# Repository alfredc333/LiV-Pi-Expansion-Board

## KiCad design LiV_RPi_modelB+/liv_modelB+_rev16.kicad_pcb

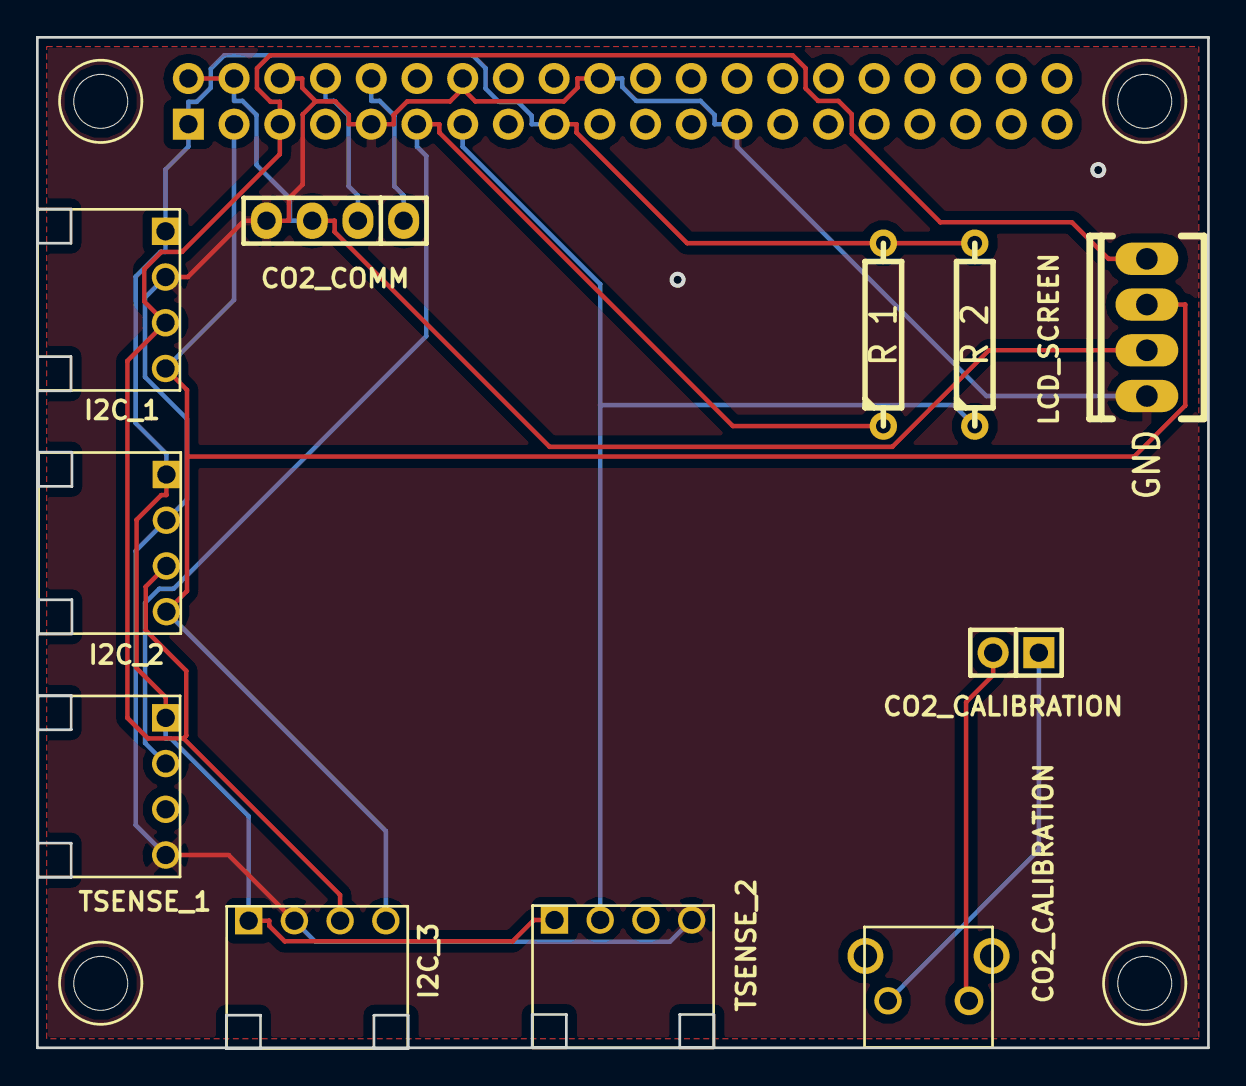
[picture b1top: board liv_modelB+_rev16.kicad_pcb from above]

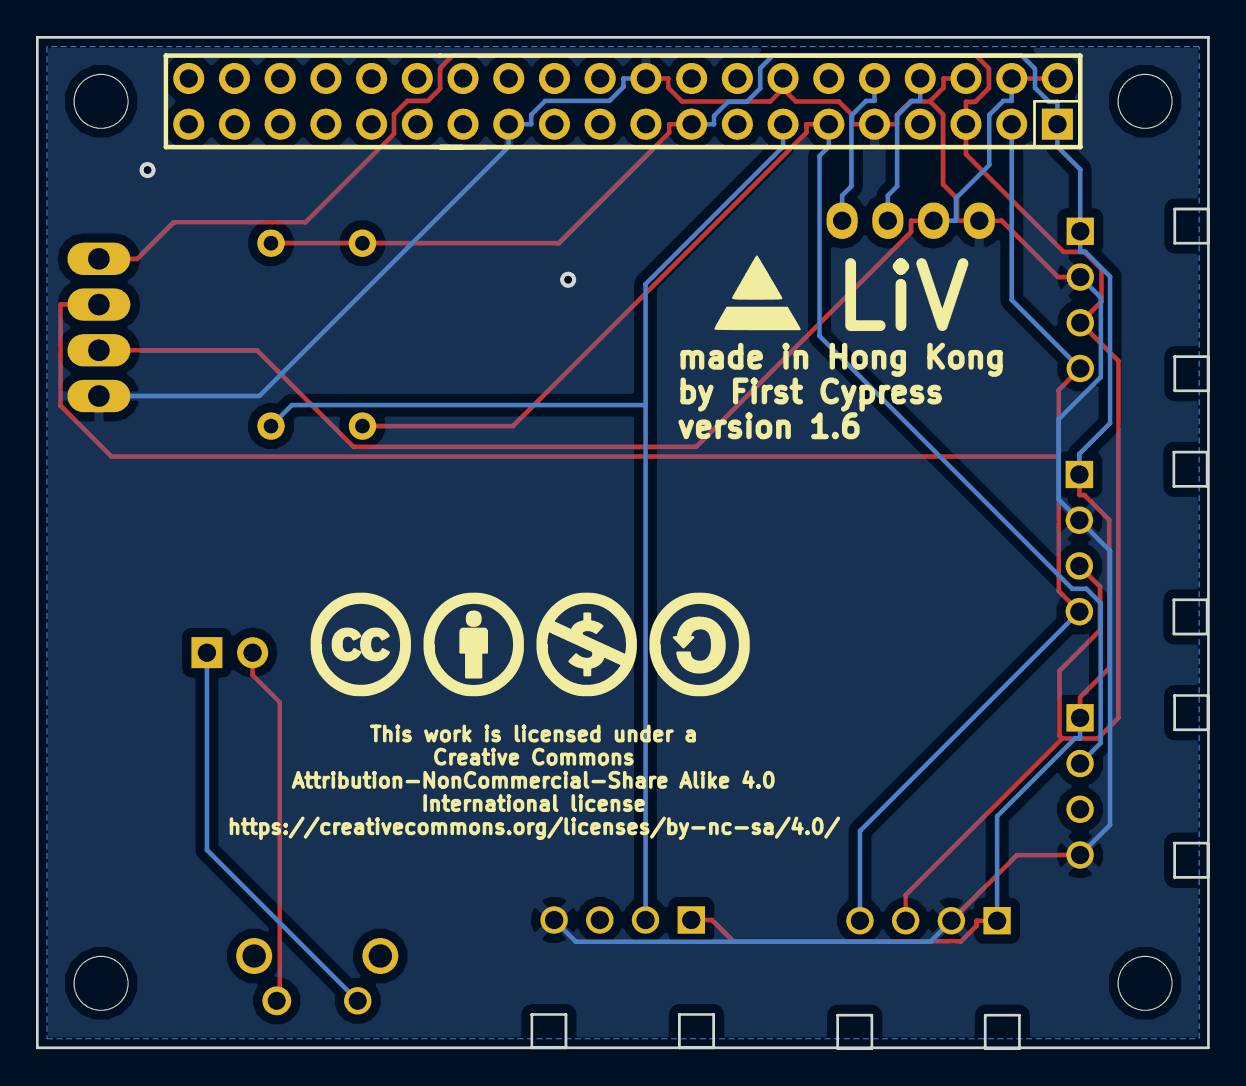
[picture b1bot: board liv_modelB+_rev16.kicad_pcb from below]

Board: 2 copper layers, 65.1 x 56.2 mm, 18 parts (3 on the bottom side), 11 nets.

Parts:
1_MNT_HOLE_RPI_PLUS, 2_MNT_HOLE_RPI_PLUS, 3_MNT_HOLE_RPI_PLUS, 4_MNT_HOLE_RPI_PLUS: mountingHole
R 1, R 2: 10k; R4
cc_by_nc_sa_logo_only: LOGO; cc_by_nc_sa_logo_only
co2_calibration1: CO2_CALIBRATION; SWITCH_TACT_RIGHT_ANGLE
co2_comm: CO2_COMM; Socket_Strip_Straight_1x04
co2_reset1: CO2_CALIBRATION; Socket_Strip_Straight_2x01
i2c_1: I2C_1; CONNECTOR_MOLEX_4PIN_RIGHT_ANGLE
i2c_2: I2C_2; CONNECTOR_MOLEX_4PIN_RIGHT_ANGLE
i2c_3: I2C_3; CONNECTOR_MOLEX_4PIN_RIGHT_ANGLE
liv_cone: LOGO; LivCypressOnlyLogo
rpi40: CONN_20X2; Socket_Strip_Straight_2x13
screen: LCD_SCREEN; Socket_MOLEX-KK-RM2-54mm_Lock_4pin_straight
temp_1: TSENSE_1; CONNECTOR_MOLEX_4PIN_RIGHT_ANGLE
temp_2: TSENSE_2; CONNECTOR_MOLEX_4PIN_RIGHT_ANGLE

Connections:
+3.3V: R 1.2, R 2.2, i2c_1.1, i2c_2.1, i2c_3.1, rpi40.1, rpi40.17, temp_1.1, temp_2.1
+5V: co2_comm.3, rpi40.2, rpi40.4, screen.2
/GPIO_2: i2c_1.4, i2c_2.4, i2c_3.4, rpi40.3, screen.3
/GPIO_3: i2c_1.3, i2c_2.3, i2c_3.3, rpi40.5, screen.4
/GPIO_14: co2_comm.2, rpi40.8
/GPIO_15: co2_comm.1, rpi40.10
/GPIO_17: R 1.1, rpi40.11, temp_1.2
/GPIO_27: R 2.1, rpi40.13, temp_2.2
GND: co2_comm.4, i2c_1.2, i2c_2.2, i2c_3.2, rpi40.6, rpi40.9, rpi40.14, rpi40.20, rpi40.25, screen.1, temp_1.4, temp_2.4
unnamed: co2_calibration1.1, co2_reset1.2
unnamed: co2_calibration1.2, co2_reset1.1

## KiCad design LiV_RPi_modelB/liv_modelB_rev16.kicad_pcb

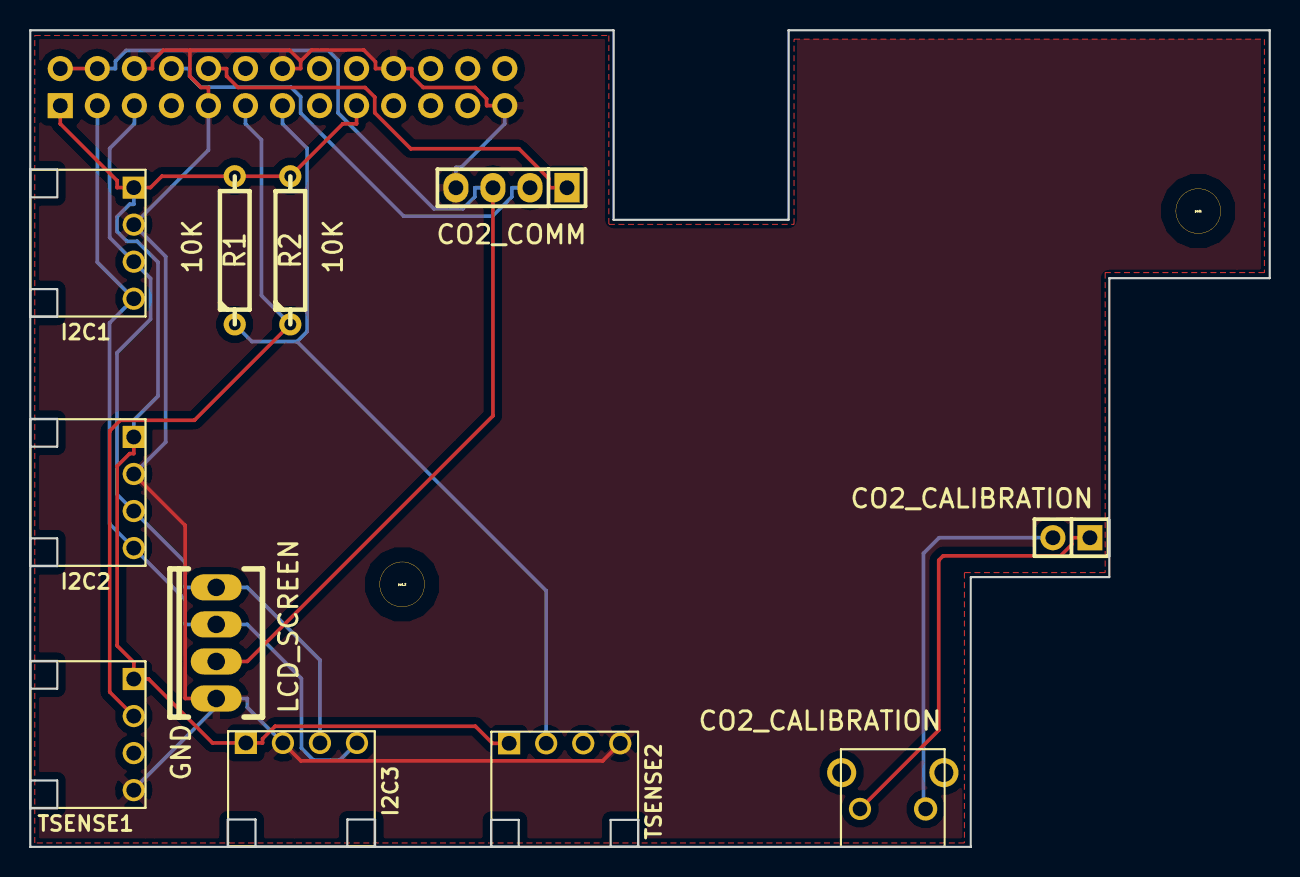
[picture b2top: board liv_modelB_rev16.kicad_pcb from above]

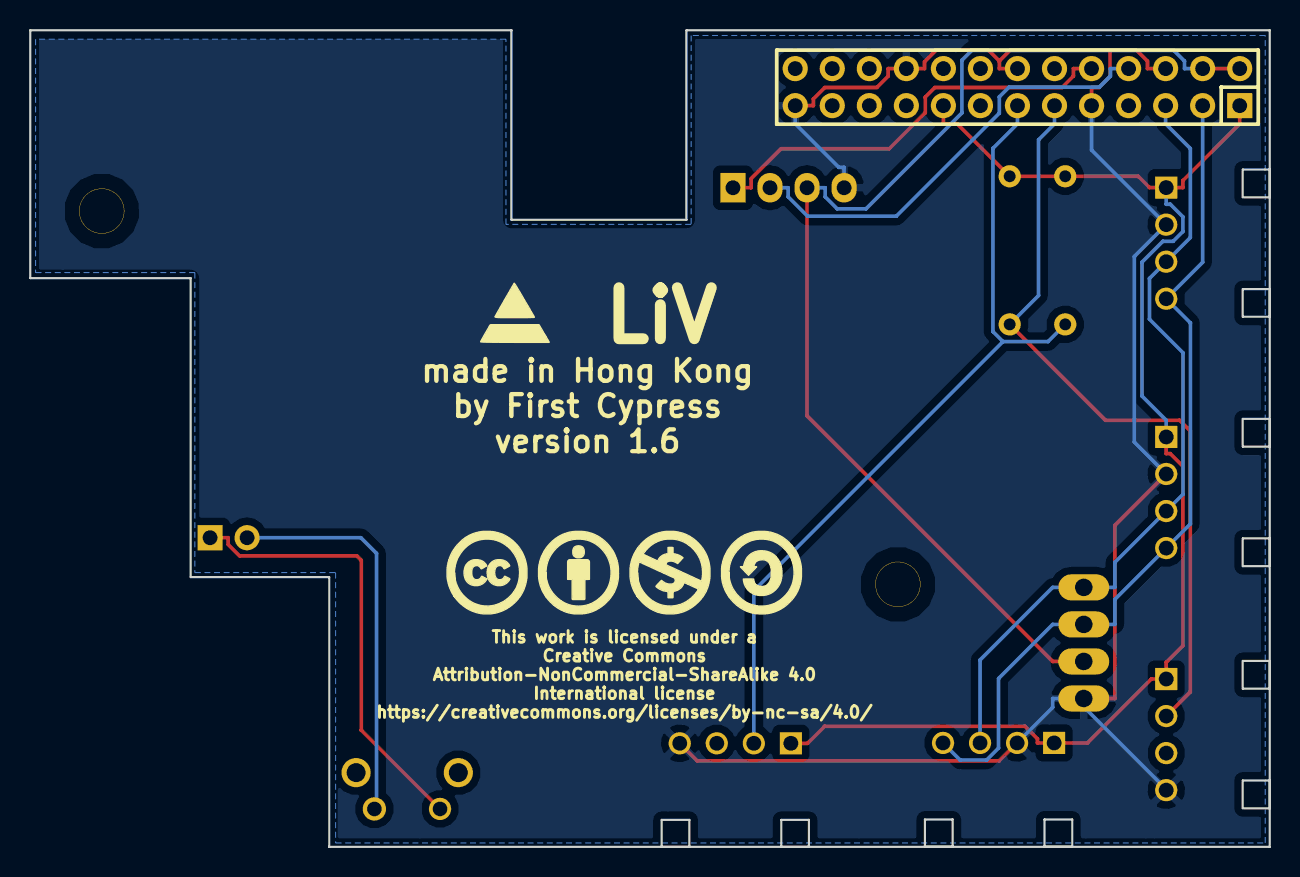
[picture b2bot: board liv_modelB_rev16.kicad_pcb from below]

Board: 2 copper layers, 85.0 x 56.0 mm, 15 parts (2 on the bottom side), 11 nets.

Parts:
P1: CONN_13X2; Socket_Strip_Straight_2x13
P3: LCD_SCREEN; Socket_MOLEX-KK-RM2-54mm_Lock_4pin_straight
P4: CO2_CALIBRATION; Socket_Strip_Straight_2x01
P5: CO2_COMM; Socket_Strip_Straight_1x04
P6: I2C1; CONNECTOR_MOLEX_4PIN_RIGHT_ANGLE
P7: I2C2; CONNECTOR_MOLEX_4PIN_RIGHT_ANGLE
P8: TSENSE2; CONNECTOR_MOLEX_4PIN_RIGHT_ANGLE
P9: TSENSE1; CONNECTOR_MOLEX_4PIN_RIGHT_ANGLE
P10: I2C3; CONNECTOR_MOLEX_4PIN_RIGHT_ANGLE
R1, R2: 10k; R4
SW1: CO2_CALIBRATION; SWITCH_TACT_RIGHT_ANGLE
cc_by_nc_sa_logo_only: LOGO; cc_by_nc_sa_logo_only
pad1: 1pin
pad_2: 1pin

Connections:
+3.3V: P1.1, P1.17, P6.1, P7.1, P8.1, P9.1, P10.1, R1.2, R2.2
+5V: P1.2, P1.4, P3.2, P5.3
/GPIO_2: P1.3, P3.3, P6.4, P7.4, P10.4
/GPIO_3: P1.5, P3.4, P6.3, P7.3, P10.3
/GPIO_14: P1.8, P5.2
/GPIO_15: P1.10, P5.1
/GPIO_17: P1.11, P9.2, R2.1
/GPIO_27: P1.13, P8.2, R1.1
GND: P1.6, P1.9, P1.14, P1.20, P1.25, P3.1, P5.4, P6.2, P7.2, P8.4, P9.4, P10.2
unnamed: P4.1, SW1.2
unnamed: P4.2, SW1.1

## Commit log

2024-03-22 LiV Pi Expansion Board
    LiV Pi Expansion board

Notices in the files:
LiV_RPi_modelB+/liv_modelB+_rev16.kicad_pcb:
This work is licensed under a
Creative Commons
Attribution-NonCommercial-Share Alike 4.0
https://creativecommons.org/licenses/by-nc-sa/4.0
